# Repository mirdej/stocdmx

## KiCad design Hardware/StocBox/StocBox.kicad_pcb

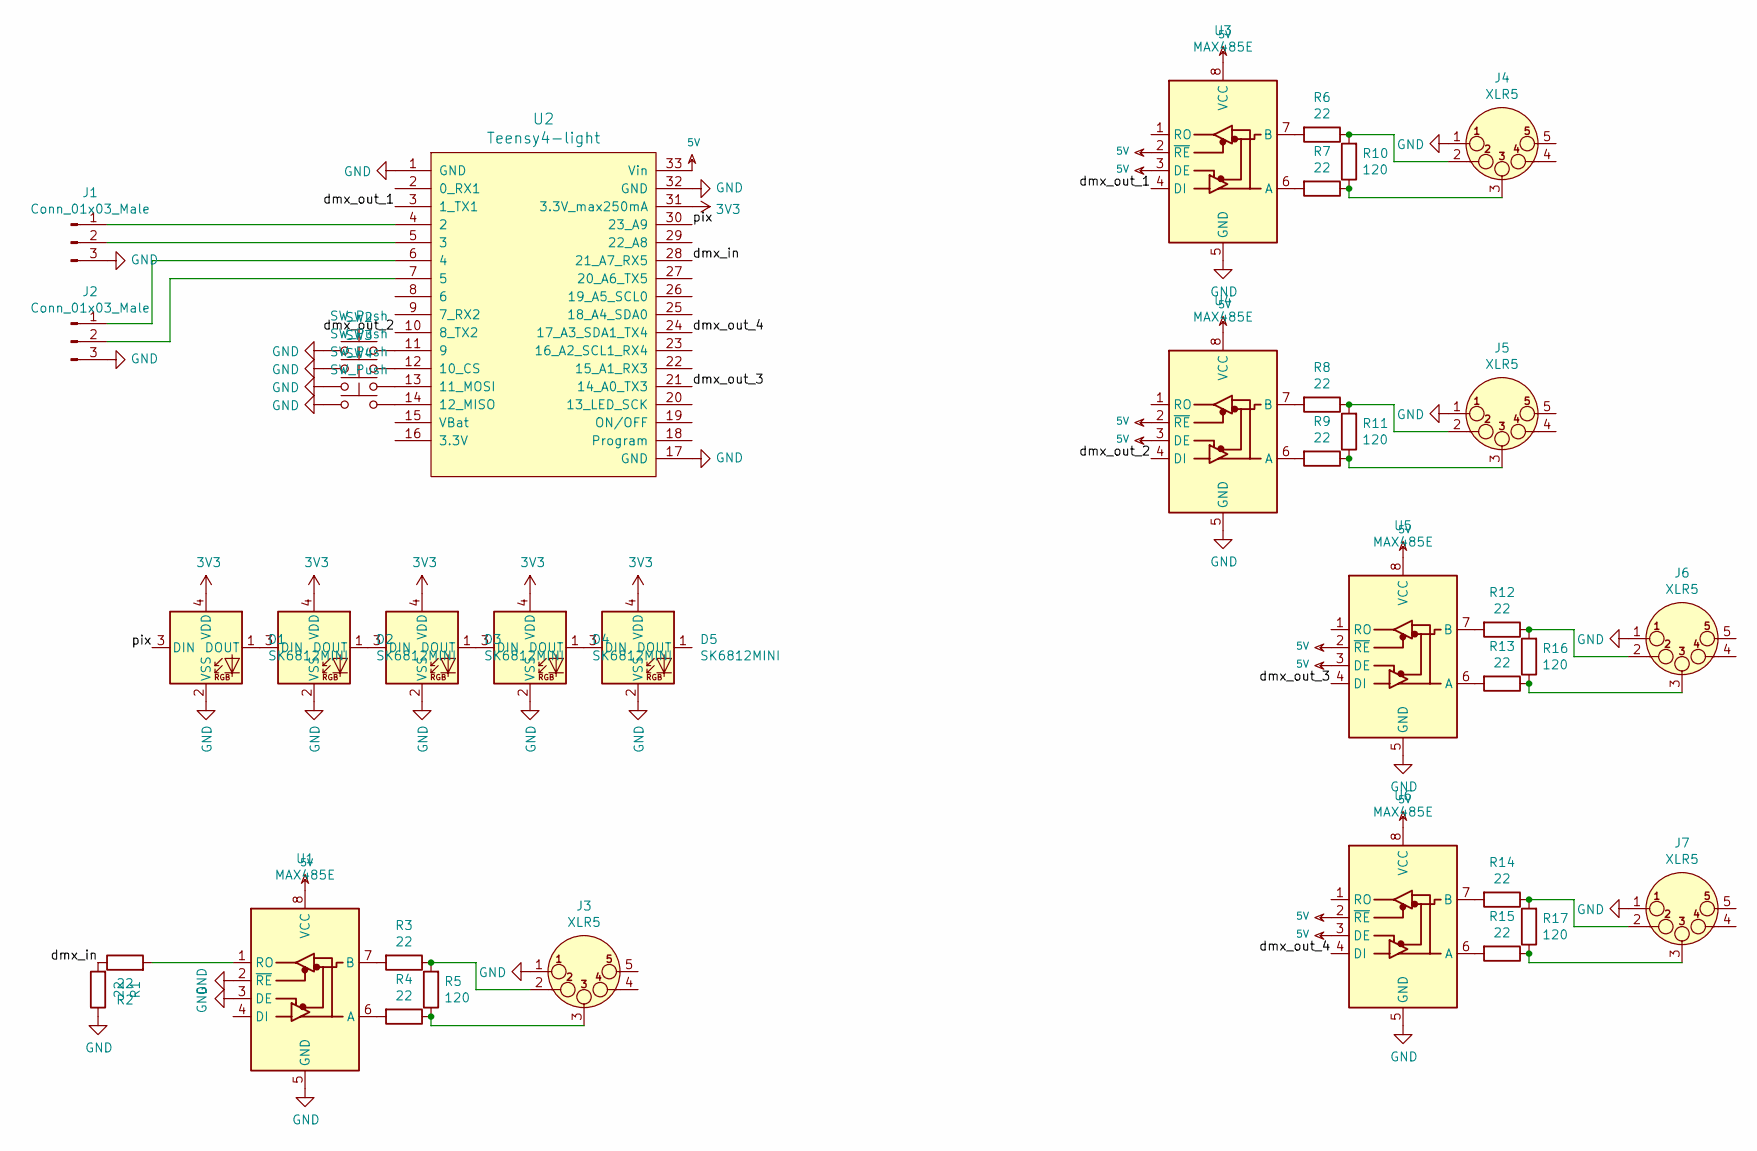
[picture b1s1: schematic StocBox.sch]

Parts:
D1, D2, D3, D4, D5: SK6812MINI; LED_SK6812MINI_PLCC4_3.5x3.5mm_P1.75mm
J1, J2: Conn_01x03_Male; Molex_KK-254_AE-6410-03A_1x03_P2.54mm_Vertical
J3: XLR5; Jack_XLR_Neutrik_NC5MAH_Horizontal
J4, J5, J6, J7: XLR5; Jack_XLR_Neutrik_NC5FAH_Horizontal
R1, R2, R3, R4, R6, R7, R8, R9, R12, R13, R14, R15: 22; R_0805_2012Metric_Pad1.15x1.40mm_HandSolder
R5, R10, R11, R16, R17: 120; R_0805_2012Metric_Pad1.15x1.40mm_HandSolder
SW1, SW2, SW3, SW4: SW_Push; Alps_Tactile_Switch
U1, U3, U4, U5, U6: MAX485E; SOIC-8_3.9x4.9mm_P1.27mm
U2: Teensy4-light; Teensy32-light

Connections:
3V3: D1.4 (VDD), D2.4 (VDD), D3.4 (VDD), D4.4 (VDD), D5.4 (VDD), U2.31 (3.3V_max250mA)
5V: U1.8 (VCC), U2.33 (Vin), U3.2 (~RE), U3.3 (DE), U3.8 (VCC), U4.2 (~RE), U4.3 (DE), U4.8 (VCC), U5.2 (~RE), U5.3 (DE), U5.8 (VCC), U6.2 (~RE), U6.3 (DE), U6.8 (VCC)
/dmx_in: R1.2, R2.1, U2.28 (21_A7_RX5)
/dmx_out_1: U2.3 (1_TX1), U3.4 (DI)
/dmx_out_2: U2.10 (8_TX2), U4.4 (DI)
/dmx_out_3: U2.21 (14_A0_TX3), U5.4 (DI)
/dmx_out_4: U2.24 (17_A3_SDA1_TX4), U6.4 (DI)
/pix: D1.3 (DIN), U2.30 (23_A9)
GND: D1.2 (VSS), D2.2 (VSS), D3.2 (VSS), D4.2 (VSS), D5.2 (VSS), J1.3, J2.3, J3.1, J4.1, J5.1, J6.1, J7.1, R1.1, SW1.1, SW2.1, SW3.1, SW4.1, U1.2 (~RE), U1.3 (DE), U1.5 (GND), U2.1 (GND), U2.17 (GND), U2.32 (GND), U3.5 (GND), U4.5 (GND), U5.5 (GND), U6.5 (GND)
unnamed: D1.1 (DOUT), D2.3 (DIN)
unnamed: D2.1 (DOUT), D3.3 (DIN)
unnamed: D3.1 (DOUT), D4.3 (DIN)
unnamed: D4.1 (DOUT), D5.3 (DIN)
unnamed: J1.1, U2.4 (2)
unnamed: J1.2, U2.5 (3)
unnamed: J2.1, U2.6 (4)
unnamed: J2.2, U2.7 (5)
unnamed: J3.2, R3.1, R5.2
unnamed: J3.3, R4.1, R5.1
unnamed: J4.2, R6.1, R10.2
unnamed: J4.3, R7.1, R10.1
unnamed: J5.2, R8.1, R11.2
unnamed: J5.3, R9.1, R11.1
unnamed: J6.2, R12.1, R16.2
unnamed: J6.3, R13.1, R16.1
unnamed: J7.2, R14.1, R17.2
unnamed: J7.3, R15.1, R17.1
unnamed: R2.2, U1.1 (RO)
unnamed: R3.2, U1.7 (B)
unnamed: R4.2, U1.6 (A)
unnamed: R6.2, U3.7 (B)
unnamed: R7.2, U3.6 (A)
unnamed: R8.2, U4.7 (B)
unnamed: R9.2, U4.6 (A)
unnamed: R12.2, U5.7 (B)
unnamed: R13.2, U5.6 (A)
unnamed: R14.2, U6.7 (B)
unnamed: R15.2, U6.6 (A)
unnamed: SW1.2, U2.11 (9)
unnamed: SW2.2, U2.12 (10_CS)
unnamed: SW3.2, U2.13 (11_MOSI)
unnamed: SW4.2, U2.14 (12_MISO)

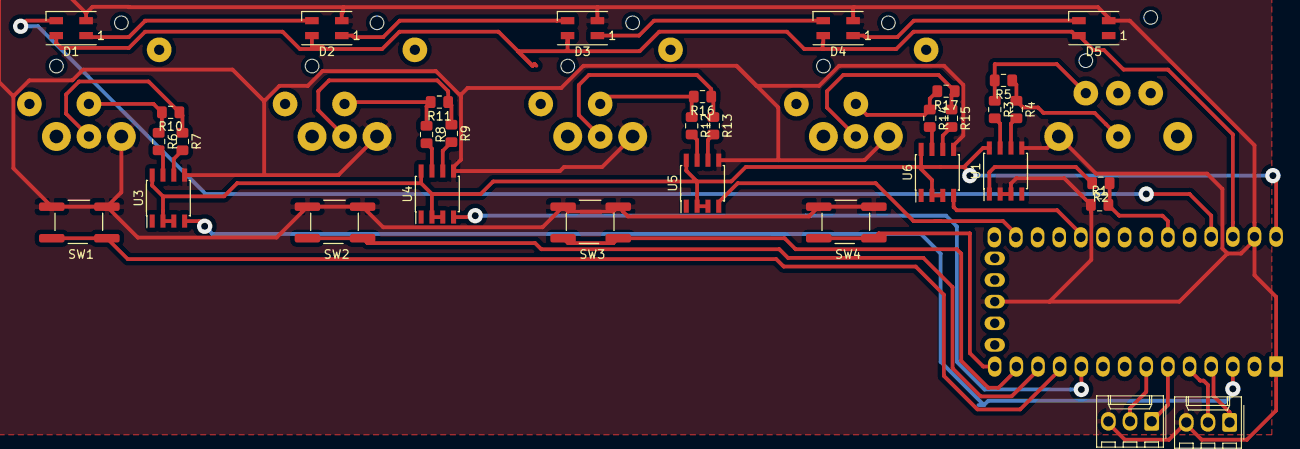
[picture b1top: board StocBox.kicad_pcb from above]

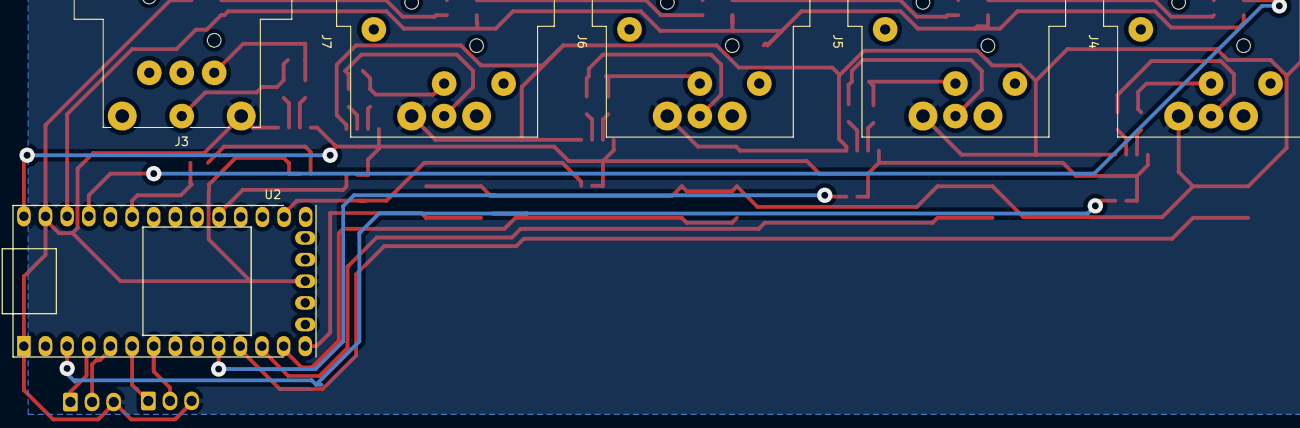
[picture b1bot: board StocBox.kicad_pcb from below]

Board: 2 copper layers, 39 parts (6 on the bottom side), 42 nets.

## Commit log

2020-02-27 basic functionality. untested
2020-02-28 add panic buffer. not connected
2020-02-28 move firmware into subfolder, add kicad files
2020-02-28 correct pin numbers, work on panic buffer implementation
2020-03-02 add metrics. usb callback. neopixel library instead of fastled
2020-03-02 return to fastled library
